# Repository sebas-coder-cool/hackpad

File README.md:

# Hackpad

This is a hackpad I built myself. A hackpad is basically a small keypad where every key does whatever you want — shortcuts, macros, or anything else you can think of.
I followed the instructions en this is him.

## BOM

[hoiddf (1).csv](https://github.com/user-attachments/files/31475726/hoiddf.1.csv)

## pictures/video's
https://github.com/user-attachments/assets/79f3460a-eb31-4a59-aa39-88dc76c06bdf

de

## design
- https://kicanvas.org/?repo=https%3A%2F%2Fgithub.com%2Fsebas-coder-cool%2Fhackpad%2Ftree%2Fmain%2Fpcb
- https://autode.sk/4gn1hyK

Made by Sebastian

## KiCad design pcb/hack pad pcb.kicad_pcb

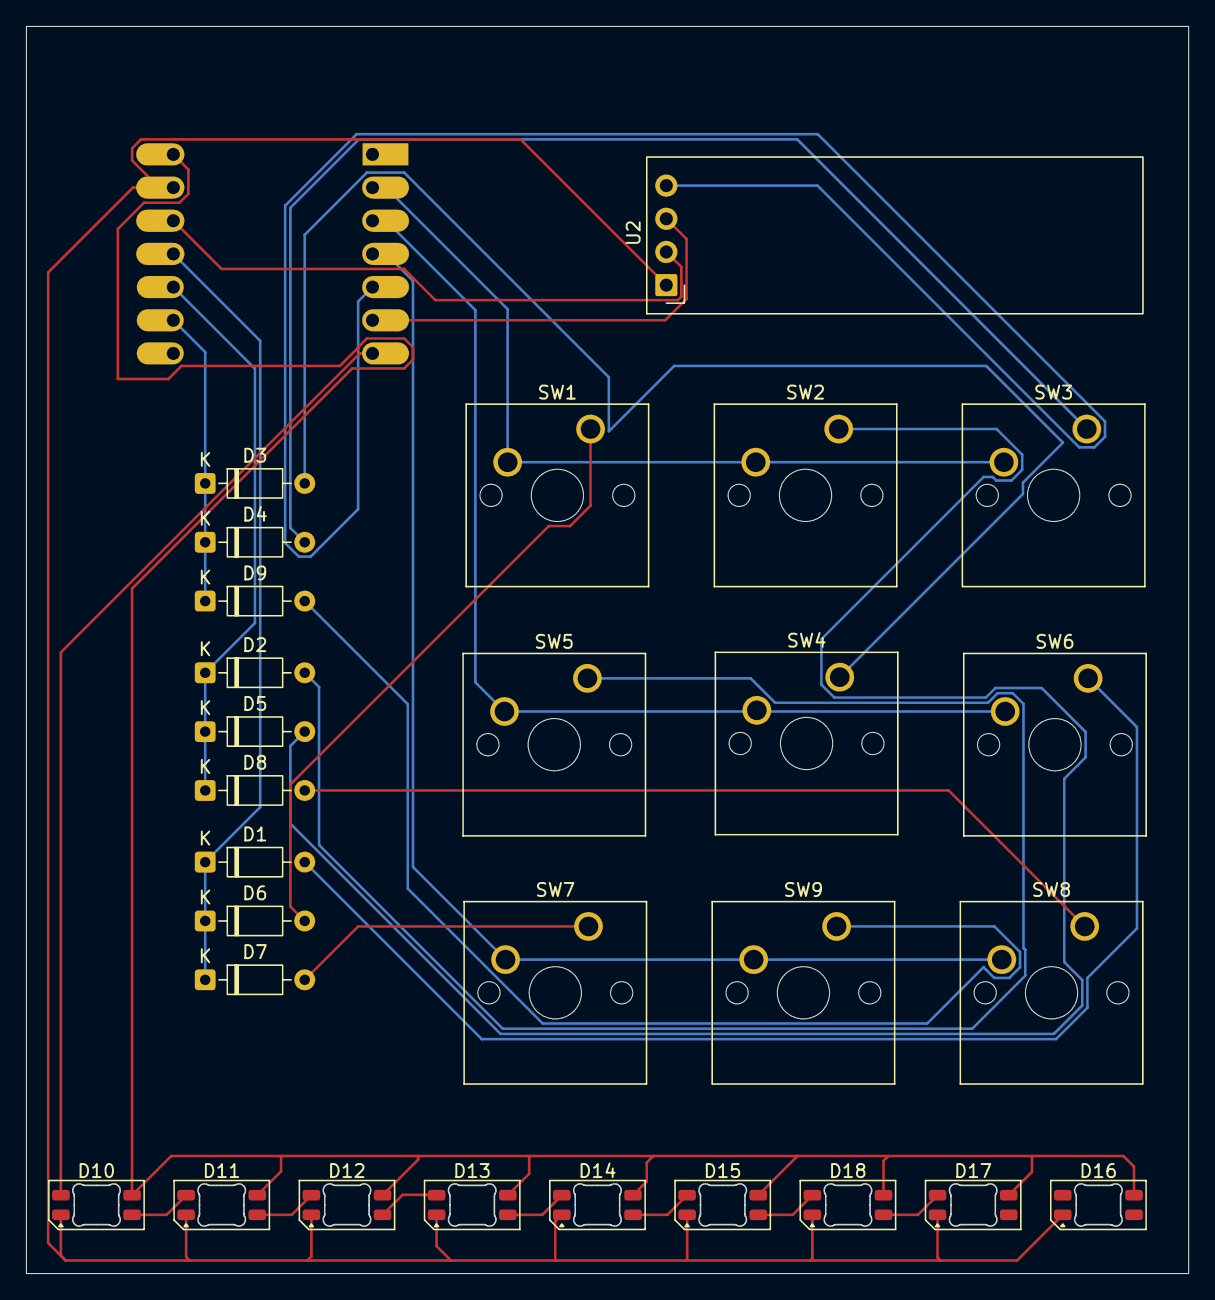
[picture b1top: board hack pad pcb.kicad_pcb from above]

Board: 2 copper layers, 89.0 x 95.5 mm, 29 parts (1 on the bottom side), 29 nets.

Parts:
D1, D2, D3, D4, D5, D6, D7, D8, D9: 1N4148; D_DO-35_SOD27_P7.62mm_Horizontal
D10, D11, D12, D13, D14, D15, D16, D17, D18: SK6812MINI-E; LED_SK6812MINI-E_3.2x2.8mm_P1.5mm_ReverseMount
SW1, SW2, SW3, SW4, SW5, SW6, SW7, SW8, SW9: SW_Push; SW_Cherry_MX_1.00u_PCB
U1: MOUDLE-SEEEDUINO-XIAO; XIAO-Generic-Hybrid-14P-2.54-21X17.8MM
U2: ER_OLEDM0.91_1x-I2C

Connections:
+3V3: U1.12 (3V3), U2.2 (VCC)
GND: D10.1 (VSS), D11.1 (VSS), D12.1 (VSS), D13.1 (VSS), D14.1 (VSS), D15.1 (VSS), D16.1 (VSS), D17.1 (VSS), D18.1 (VSS), U1.13 (GND), U2.1 (GND)
unnamed: D1.2 (A), SW6.1
unnamed: D1.1 (K), D6.1 (K), D7.1 (K), U1.11 (PA6_A10_D10_MOSI)
unnamed: D2.2 (A), SW5.1
unnamed: D2.1 (K), D5.1 (K), D8.1 (K), U1.10 (PA5_A9_D9_MISO)
unnamed: D3.2 (A), SW4.1
unnamed: D3.1 (K), D4.1 (K), D9.1 (K), U1.9 (PA7_A8_D8_SCK)
unnamed: D4.2 (A), SW3.1
unnamed: D5.2 (A), SW2.1
unnamed: D6.2 (A), SW1.1
unnamed: D7.2 (A), SW7.1
unnamed: D8.2 (A), SW8.1
unnamed: D9.2 (A), SW9.1
unnamed: D10.2 (DIN), U1.7 (PB08_A6_D6_TX)
unnamed: D10.4 (DOUT), D11.2 (DIN)
unnamed: D10.3 (VDD), D11.3 (VDD), D12.3 (VDD), D13.3 (VDD), D14.3 (VDD), D15.3 (VDD), D16.3 (VDD), D17.3 (VDD), D18.3 (VDD), U1.14 (5V)
unnamed: D11.4 (DOUT), D12.2 (DIN)
unnamed: D12.4 (DOUT), D13.2 (DIN)
unnamed: D13.4 (DOUT), D14.2 (DIN)
unnamed: D14.4 (DOUT), D15.2 (DIN)
unnamed: D15.4 (DOUT), D18.2 (DIN)
unnamed: D16.2 (DIN), D17.4 (DOUT)
unnamed: D17.2 (DIN), D18.4 (DOUT)
unnamed: SW1.2, SW2.2, SW3.2, U1.2 (PA4_A1_D1)
unnamed: U1.5 (PA8_A4_D4_SDA), U2.4 (SDA)
unnamed: U1.6 (PA9_A5_D5_SCL), U2.3 (SCL)
unnamed: SW4.2, SW5.2, SW6.2, U1.3 (PA10_A2_D2)
unnamed: SW7.2, SW8.2, SW9.2, U1.4 (PA11_A3_D3)
